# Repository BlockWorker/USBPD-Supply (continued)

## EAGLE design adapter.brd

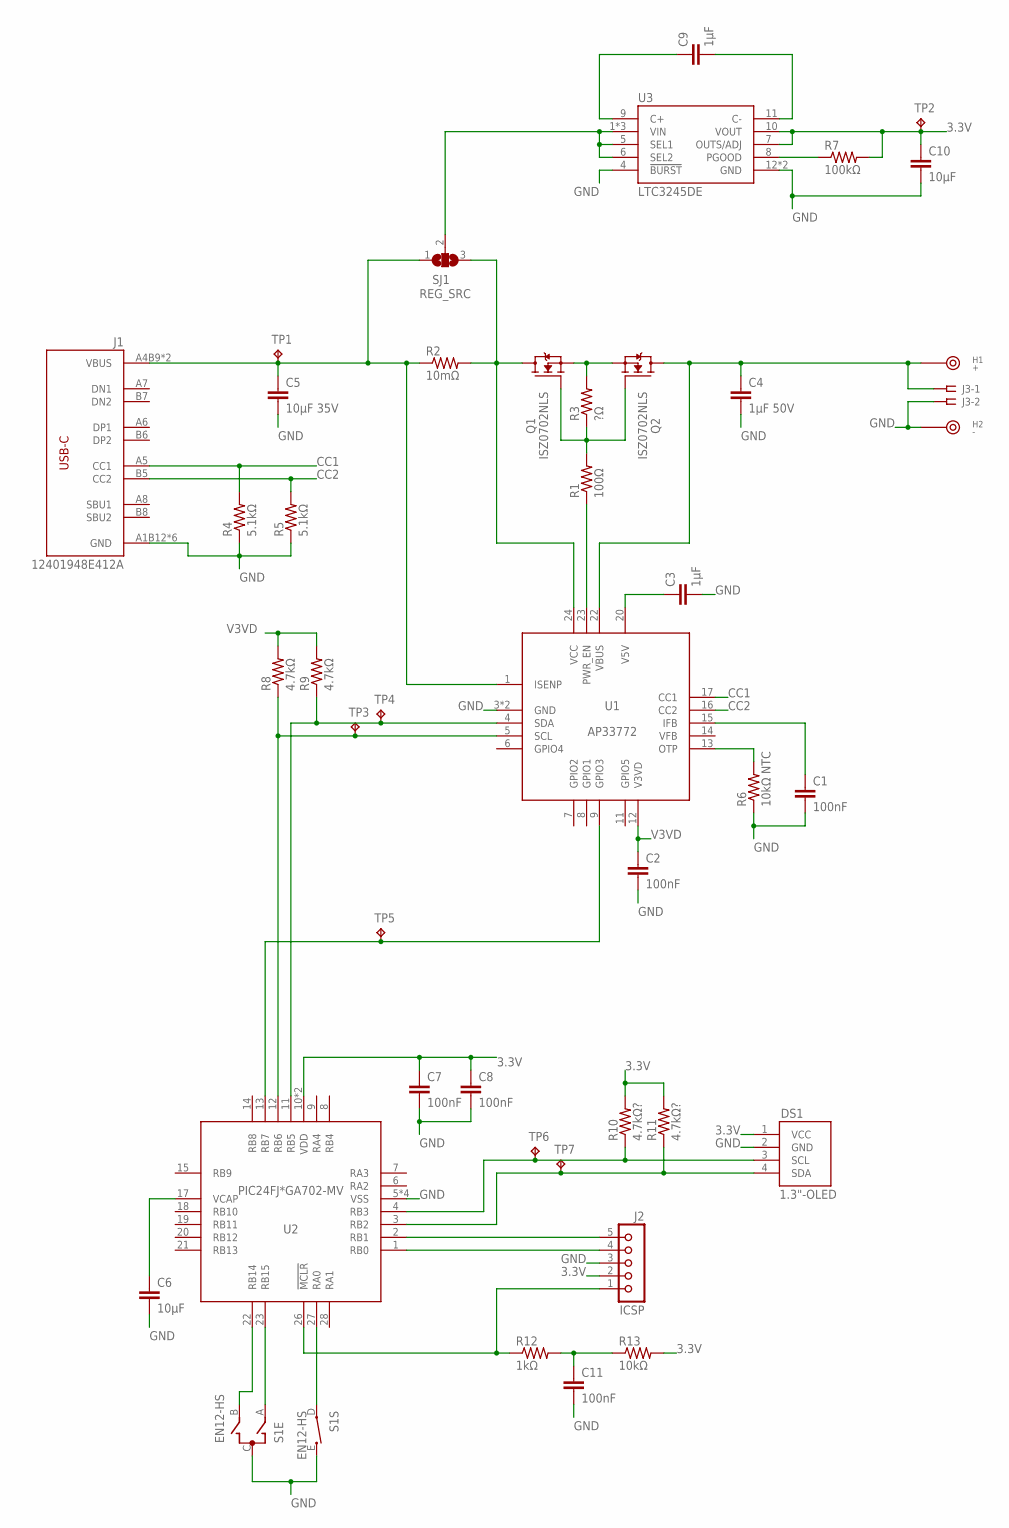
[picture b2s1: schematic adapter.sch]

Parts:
C1, C2, C7, C8, C11: 100nF; C0603
C3, C9: 1µF; C0603
C4: 1µF 50V; C0603
C5: 10µF 35V; C1206
C6, C10: 10µF; C0805
DS1: 1.3"-OLED
H1: +; 78614015360
H2: -; 78614015360
J1: 12401948E412A
J2: ICSP; 5PIN-1.27
J3: SSW-102-02-G-S-RA
Q1, Q2: ISZ0702NLS; TSDSON-8
R1: 100Ω; R0603
R2: 10mΩ; R1206
R3: ?Ω; R0603
R4, R5: 5.1kΩ; R0603
R6: 10kΩ NTC; R0603
R7: 100kΩ; R0603
R8, R9: 4.7kΩ; R0603
R10, R11: 4.7kΩ?; R0603
R12: 1kΩ; R0603
R13: 10kΩ; R0603
S1: EN12-HS
SJ1: REG_SRC; SJ_2
TP1, TP2, TP3, TP4, TP5, TP6, TP7: RCU-0(J); TP_0603_JOINED
U1: AP33772; QFN24-4X4
U2: PIC24FJ*GA702-MV; UQFN28_4X4MM
U3: LTC3245DE; DFN12

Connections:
3.3V: C7.1, C8.1, C10.1, DS1.1 (VCC), J2.2, R7.2, R10.2, R11.2, R13.2, TP2.1, U2.10 (VDD), U2.25 (VDD), U3.7 (OUTS/ADJ), U3.10 (VOUT)
!MCLR: J2.1, R12.1, U2.26 (!MCLR)
!MCLR!_FILTER: C11.1, R12.2, R13.1
C+: C9.1, U3.9 (C+)
C-: C9.2, U3.11 (C-)
CC1: J1.A5 (CC1), R4.2, U1.17 (CC1)
CC2: J1.B5 (CC2), R5.2, U1.16 (CC2)
ENC_A: S1.A, U2.23 (RB15)
ENC_B: S1.B, U2.22 (RB14)
ENC_SW: S1.D (1), U2.27 (RA0)
GND: C1.2, C2.2, C3.2, C4.2, C5.2, C6.2, C7.2, C8.2, C10.2, C11.2, DS1.2 (GND), H2.M, J1.A1B12 (GND), J1.B1A12 (GND), J1.M1 (GND), J1.M2 (GND), J1.M3 (GND), J1.M4 (GND), J2.3, J3.2, R4.1, R5.1, R6.1, S1.C, S1.E (2), U1.3 (GND), U1.EXP (GND), U2.5 (VSS), U2.16 (VSS), U2.24 (VSS), U2.TH (VSS), U3.4 (!BURST), U3.12 (GND), U3.EXP (GND)
IFB: C1.1, U1.15 (IFB)
OLED_SCL: DS1.3 (SCL), R10.1, TP6.1, U2.4 (RB3)
OLED_SDA: DS1.4 (SDA), R11.1, TP7.1, U2.3 (RB2)
OTP: R6.2, U1.13 (OTP)
PGC: J2.5, U2.2 (RB1)
PGD: J2.4, U2.1 (RB0)
PWR_EN: R1.1, U1.23 (PWR_EN)
PWR_EN_R: Q1.4 (G), Q2.4 (G), R1.2, R3.1
REG_PGOOD: R7.1, U3.8 (PGOOD)
REG_VIN: SJ1.2, U3.1 (VIN), U3.2 (VIN), U3.3 (VIN), U3.5 (SEL1), U3.6 (SEL2)
USB_INT: TP5.1, U1.9 (GPIO3), U2.13 (RB7)
USB_SCL: R8.1, TP3.1, U1.5 (SCL), U2.12 (RB6)
USB_SDA: R9.1, TP4.1, U1.4 (SDA), U2.11 (RB5)
V3VD: C2.1, R8.2, R9.2, U1.12 (V3VD)
V5V: C3.1, U1.20 (V5V)
VBUS_IN: C5.1, J1.A4B9 (VBUS), J1.B4A9 (VBUS), R2.1, SJ1.1, TP1.1, U1.1 (ISENP)
VBUS_IN_R: Q1.5-8 (D), R2.2, SJ1.3, U1.24 (VCC)
VBUS_OUT: C4.1, H1.M, J3.1, Q2.5-8 (D), U1.22 (VBUS)
VBUS_SW: Q1.1 (S), Q1.2 (S), Q1.3 (S), Q2.1 (S), Q2.2 (S), Q2.3 (S), R3.2
VCAP: C6.1, U2.17 (VCAP)

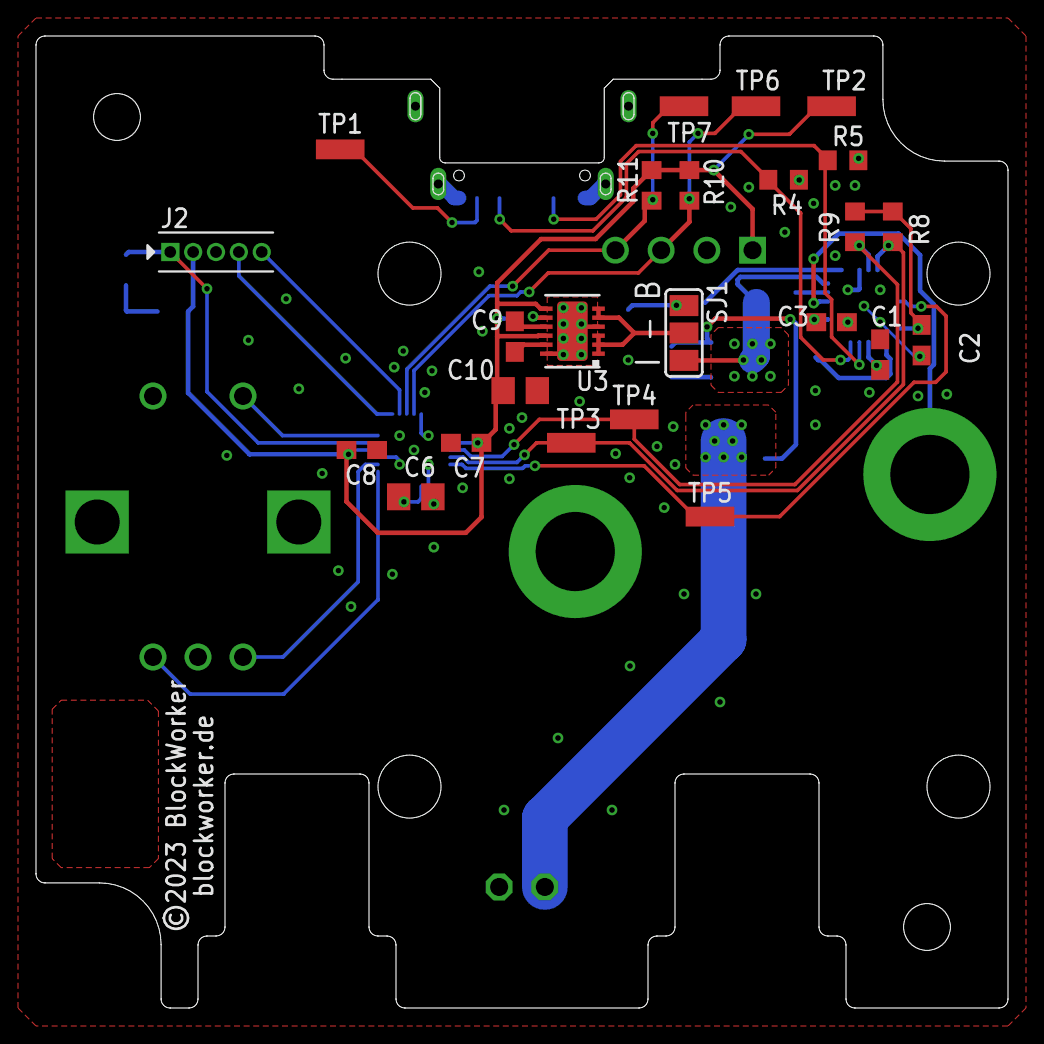
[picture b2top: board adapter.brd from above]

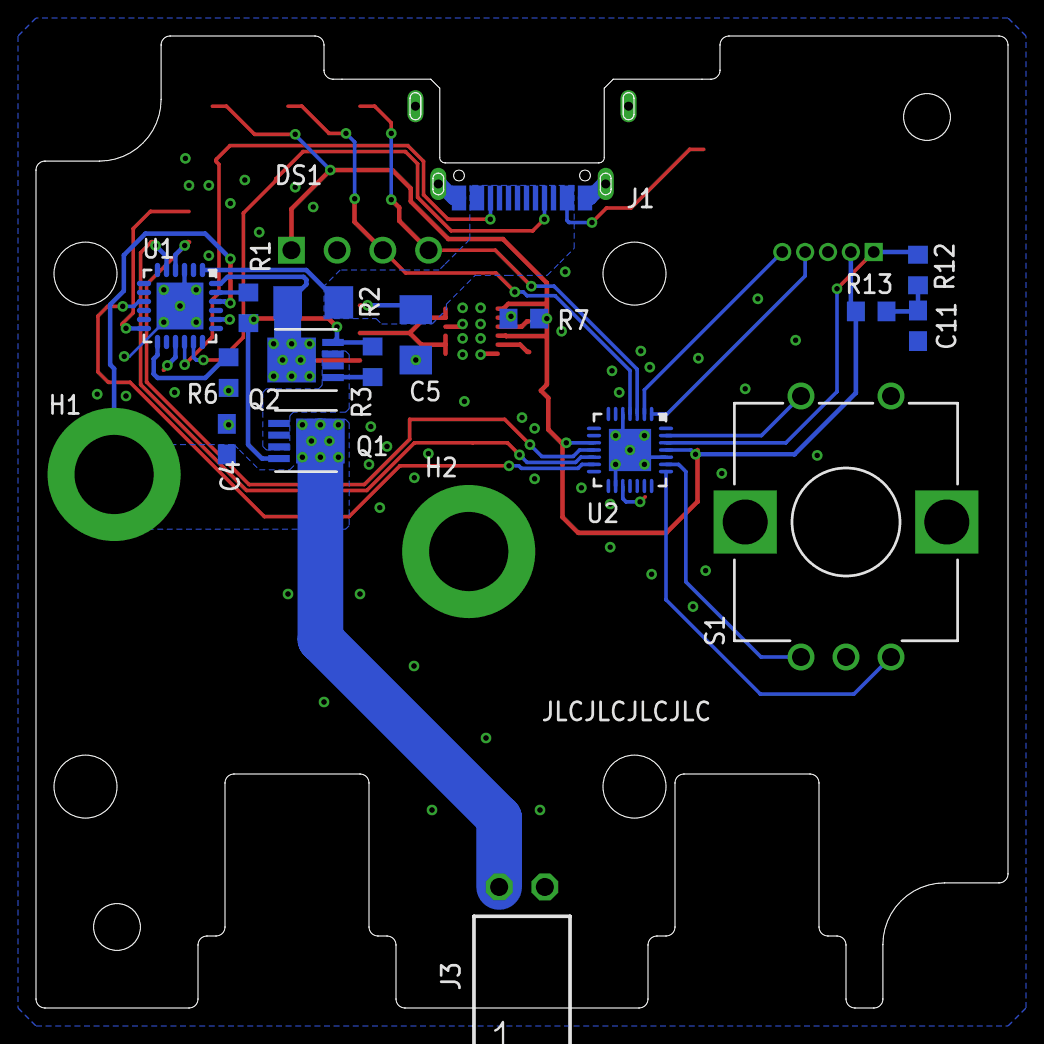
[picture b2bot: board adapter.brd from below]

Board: 2 copper layers, 54.0 x 54.0 mm, 44 parts (20 on the bottom side), 31 nets.

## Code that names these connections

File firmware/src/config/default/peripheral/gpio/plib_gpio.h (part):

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#define LCD_CS_N_Get()               ((PORTB >> 8) & 0x1U)
#define LCD_CS_N_PIN                  GPIO_PIN_RB8

/*** Macros for LCD_MOSI pin ***/
#define LCD_MOSI_Get()               ((PORTB >> 9) & 0x1U)
#define LCD_MOSI_PIN                  GPIO_PIN_RB9

/*** Macros for LCD_MISO pin ***/
#define LCD_MISO_Get()               ((PORTB >> 10) & 0x1U)
#define LCD_MISO_PIN                  GPIO_PIN_RB10

/*** Macros for LCD_SCK pin ***/
#define LCD_SCK_Get()               ((PORTB >> 14) & 0x1U)
#define LCD_SCK_PIN                  GPIO_PIN_RB14

/*** Macros for USB1_ALERT_N pin ***/
#define USB1_ALERT_N_Get()               ((PORTF >> 5) & 0x1U)
#define USB1_ALERT_N_PIN                  GPIO_PIN_RF5

/*** Macros for USB1_SDA pin ***/
#define USB1_SDA_Get()               ((PORTD >> 9) & 0x1U)
#define USB1_SDA_PIN                  GPIO_PIN_RD9

/*** Macros for USB1_SCL pin ***/
#define USB1_SCL_Get()               ((PORTD >> 10) & 0x1U)
#define USB1_SCL_PIN                  GPIO_PIN_RD10

/*** Macros for USB1_EN pin ***/
#define USB1_EN_Set()               (LATDSET = (1U<<11))
#define USB1_EN_Clear()             (LATDCLR = (1U<<11))
#define USB1_EN_Toggle()            (LATDINV= (1U<<11))
#define USB1_EN_OutputEnable()      (TRISDCLR = (1U<<11))
#define USB1_EN_InputEnable()       (TRISDSET = (1U<<11))
#define USB1_EN_Get()               ((PORTD >> 11) & 0x1U)
#define USB1_EN_PIN                  GPIO_PIN_RD11

/*** Macros for USB2_ALERT_N pin ***/
#define USB2_ALERT_N_Get()               ((PORTD >> 1) & 0x1U)
#define USB2_ALERT_N_PIN                  GPIO_PIN_RD1

/*** Macros for USB2_SDA pin ***/
#define USB2_SDA_Get()               ((PORTD >> 2) & 0x1U)
#define USB2_SDA_PIN                  GPIO_PIN_RD2

/*** Macros for USB2_SCL pin ***/
#define USB2_SCL_Get()               ((PORTD >> 3) & 0x1U)
#define USB2_SCL_PIN                  GPIO_PIN_RD3

/*** Macros for USB2_EN pin ***/
#define USB2_EN_Set()               (LATDSET = (1U<<4))
#define USB2_EN_Clear()             (LATDCLR = (1U<<4))
#define USB2_EN_Toggle()            (LATDINV= (1U<<4))
#define USB2_EN_OutputEnable()      (TRISDCLR = (1U<<4))
#define USB2_EN_InputEnable()       (TRISDSET = (1U<<4))
#define USB2_EN_Get()               ((PORTD >> 4) & 0x1U)
#define USB2_EN_PIN                  GPIO_PIN_RD4


// *****************************************************************************
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
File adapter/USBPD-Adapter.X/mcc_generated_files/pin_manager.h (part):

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*/
/**
  @Summary
    Sets the GPIO pin, RA0, high using LATA0.

  @Description
    Sets the GPIO pin, RA0, high using LATA0.

  @Preconditions
    The RA0 must be set to an output.
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#define ENC_SW_SetHigh()          (_LATA0 = 1)
/**
  @Summary
    Sets the GPIO pin, RA0, low using LATA0.

  @Description
    Sets the GPIO pin, RA0, low using LATA0.

  @Preconditions
    The RA0 must be set to an output.
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#define ENC_SW_SetLow()           (_LATA0 = 0)
/**
  @Summary
    Toggles the GPIO pin, RA0, using LATA0.

  @Description
    Toggles the GPIO pin, RA0, using LATA0.

  @Preconditions
    The RA0 must be set to an output.
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#define ENC_SW_Toggle()           (_LATA0 ^= 1)
/**
  @Summary
    Reads the value of the GPIO pin, RA0.

  @Description
    Reads the value of the GPIO pin, RA0.

  @Preconditions
    None.
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    </code>

*/
#define ENC_SW_GetValue()         _RA0
/**
  @Summary
    Configures the GPIO pin, RA0, as an input.

  @Description
    Configures the GPIO pin, RA0, as an input.

  @Preconditions
    None.
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#define ENC_SW_SetDigitalInput()  (_TRISA0 = 1)
/**
  @Summary
    Configures the GPIO pin, RA0, as an output.

  @Description
    Configures the GPIO pin, RA0, as an output.

  @Preconditions
    None.
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#define ENC_SW_SetDigitalOutput() (_TRISA0 = 0)
/**
  @Summary
    Sets the GPIO pin, RB14, high using LATB14.

  @Description
    Sets the GPIO pin, RB14, high using LATB14.

  @Preconditions
    The RB14 must be set to an output.
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#define ENC_B_SetHigh()          (_LATB14 = 1)
/**
  @Summary
    Sets the GPIO pin, RB14, low using LATB14.

  @Description
    Sets the GPIO pin, RB14, low using LATB14.

  @Preconditions
    The RB14 must be set to an output.
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#define ENC_B_SetLow()           (_LATB14 = 0)
/**
  @Summary
    Toggles the GPIO pin, RB14, using LATB14.

  @Description
    Toggles the GPIO pin, RB14, using LATB14.

  @Preconditions
    The RB14 must be set to an output.
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#define ENC_B_Toggle()           (_LATB14 ^= 1)
/**
  @Summary
    Reads the value of the GPIO pin, RB14.

  @Description
    Reads the value of the GPIO pin, RB14.

  @Preconditions
    None.
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    </code>

*/
#define ENC_B_GetValue()         _RB14
/**
  @Summary
    Configures the GPIO pin, RB14, as an input.

  @Description
    Configures the GPIO pin, RB14, as an input.

  @Preconditions
    None.
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#define ENC_B_SetDigitalInput()  (_TRISB14 = 1)
/**
  @Summary
    Configures the GPIO pin, RB14, as an output.

  @Description
    Configures the GPIO pin, RB14, as an output.

  @Preconditions
    None.
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#define ENC_B_SetDigitalOutput() (_TRISB14 = 0)
/**
  @Summary
    Sets the GPIO pin, RB15, high using LATB15.

  @Description
    Sets the GPIO pin, RB15, high using LATB15.

  @Preconditions
    The RB15 must be set to an output.
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#define ENC_A_SetHigh()          (_LATB15 = 1)
/**
  @Summary
    Sets the GPIO pin, RB15, low using LATB15.

  @Description
    Sets the GPIO pin, RB15, low using LATB15.

  @Preconditions
    The RB15 must be set to an output.
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#define ENC_A_SetLow()           (_LATB15 = 0)
/**
  @Summary
    Toggles the GPIO pin, RB15, using LATB15.

  @Description
    Toggles the GPIO pin, RB15, using LATB15.

  @Preconditions
    The RB15 must be set to an output.
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#define ENC_A_Toggle()           (_LATB15 ^= 1)
/**
  @Summary
    Reads the value of the GPIO pin, RB15.

  @Description
    Reads the value of the GPIO pin, RB15.

  @Preconditions
    None.
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    </code>

*/
#define ENC_A_GetValue()         _RB15
/**
  @Summary
    Configures the GPIO pin, RB15, as an input.

  @Description
    Configures the GPIO pin, RB15, as an input.

  @Preconditions
    None.
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#define ENC_A_SetDigitalInput()  (_TRISB15 = 1)
/**
  @Summary
    Configures the GPIO pin, RB15, as an output.

  @Description
    Configures the GPIO pin, RB15, as an output.

  @Preconditions
    None.
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#define ENC_A_SetDigitalOutput() (_TRISB15 = 0)
/**
  @Summary
    Sets the GPIO pin, RB7, high using LATB7.

  @Description
    Sets the GPIO pin, RB7, high using LATB7.

  @Preconditions
    The RB7 must be set to an output.
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#define USB_INT_SetHigh()          (_LATB7 = 1)
/**
  @Summary
    Sets the GPIO pin, RB7, low using LATB7.

  @Description
    Sets the GPIO pin, RB7, low using LATB7.

  @Preconditions
    The RB7 must be set to an output.
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#define USB_INT_SetLow()           (_LATB7 = 0)
/**
  @Summary
    Toggles the GPIO pin, RB7, using LATB7.

  @Description
    Toggles the GPIO pin, RB7, using LATB7.

  @Preconditions
    The RB7 must be set to an output.
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#define USB_INT_Toggle()           (_LATB7 ^= 1)
/**
  @Summary
    Reads the value of the GPIO pin, RB7.

  @Description
    Reads the value of the GPIO pin, RB7.

  @Preconditions
    None.
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    </code>

*/
#define USB_INT_GetValue()         _RB7
/**
  @Summary
    Configures the GPIO pin, RB7, as an input.

  @Description
    Configures the GPIO pin, RB7, as an input.

  @Preconditions
    None.
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#define USB_INT_SetDigitalInput()  (_TRISB7 = 1)
/**
  @Summary
    Configures the GPIO pin, RB7, as an output.

  @Description
    Configures the GPIO pin, RB7, as an output.

  @Preconditions
    None.
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
/**
  @Summary
    Callback for ENC_SW Pin.

  @Description
    This routine is callback for ENC_SW Pin

  @Param
    None.
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
/**
  @Summary
    Callback for USB_INT Pin.

  @Description
    This routine is callback for USB_INT Pin

  @Param
    None.
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
/**
  @Summary
    Callback for ENC_A Pin.

  @Description
    This routine is callback for ENC_A Pin

  @Param
    None.
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
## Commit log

2023-04-05 Initial commit, basic design up to first USB port
2023-04-08 Added firmware base, layout in progress
2023-04-12 Supply PCB done (?)
2023-05-07 Base design complete, adapter firmware started
